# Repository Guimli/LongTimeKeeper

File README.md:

# LongTimeKeeper

**LongTimeKeeper** is a drop-in replacement for the STMicroelectronics **M48T58 / M48T58Y TIMEKEEPER® NVRAM** (8 K × 8 battery-backed SRAM with real-time clock) in its 28-pin 600 mil PCDIP "CAPHAT" package.

The original PCDIP part has its lithium cell sealed in the package. When the cell runs flat, the chip loses both the clock and the SRAM contents, and the whole IC has to be replaced. LongTimeKeeper uses the surface-mount **M48T58Y in SOH28** instead. That package normally takes an ST SNAPHAT® battery/crystal top. Here the SNAPHAT is replaced by:

- a discrete **32.768 kHz crystal**, and
- a **user-replaceable 1/2 AA 3.6 V lithium cell** in a Keystone holder. The cell is a Tadiran **SL-850/S** from the SL-800 XOL (eXtended Operating Life) series, rated 1.2 Ah. This series has a very low self-discharge rate.

The cell has a much larger capacity than the original internal cell, and you can swap it without desoldering anything or losing the board's socketed footprint.

## How it works

The adapter is a stack of two PCBs:

| Board | KiCad project | Role |
|---|---|---|
| **Bottom** | `LongTimeKeeper_Bottom/LongTimekeeper_Bottom.kicad_pro` | DIP-28 (15.24 mm) pin-out that plugs into the original M48T58 socket. It carries the M48T58Y-SOH28 (U7), the 32.768 kHz crystal (Y1) on the SNAPHAT X1/X2 contacts, and a 4-pad battery connector (BT1) wired to the SNAPHAT BAT+/BAT- contacts. |
| **Up** (battery) | `LongTimeKeeper_Up/TimekeeperBat_Up.kicad_pro` | Carries the Keystone 108 1/2 AA holder with its 108C cover (BT1). It connects to the bottom board through 4 × 2.54 mm pins (J1, `Battery_PCB` footprint), which also hold the two boards together mechanically. |

Signal mapping: every DIP-28 pin of the original package (A0–A12, DQ0–DQ7, Ē1, E2, Ḡ, W̄, FT, VCC, VSS) is routed 1:1 to the matching pin of the SOH28 device, so the host system sees an unmodified M48T58. Both boards are 2-layer, 1.6 mm FR-4, and fit within the original DIP-28 footprint (about 18.4 × 36.3 mm).

The projects were created with **KiCad 10**.

## Bill of materials

Prices are **indicative, VAT included (TTC, 20 % French VAT), for 1 unit**, checked in October 2026 at DigiKey France, except where noted. Distributor prices change often, so check them before ordering.

| Qty | Ref. | Description | Manufacturer | Manufacturer P/N | Unit price TTC | Total TTC |
|---:|---|---|---|---|---:|---:|
| 1 | U7 | TIMEKEEPER® NVRAM 64 Kbit (8K×8) + RTC, 5 V, SOH28 (SNAPHAT socket) | STMicroelectronics | **M48T58Y-70MH1F** | 24.97 € | 24.97 € |
| 1 | Y1 | Crystal 32.768 kHz, ±20 ppm, 12.5 pF, SMD 3.2 × 1.5 mm (3215) | Epson | **FC-135 32.7680KA-A3** (Q13FC1350000400) | 2.81 € | 2.81 € |
| 1 | BT1 (Up) | Battery holder, 1 × 1/2 AA, through-hole | Keystone Electronics | **108** | 1.52 € | 1.52 € |
| 1 | BT1 (Up) | Battery holder cover, 1/2 AA | Keystone Electronics | **108C** | ≈ 0.58 € ¹ | 0.58 € |
| 1 | — | Lithium cell Li-SOCl₂ 3.6 V 1.2 Ah, 1/2 AA (ER14250), standard terminals (no tabs), **SL-800 XOL – extended operating life** (very low self-discharge) | Tadiran | **SL-850/S** | 14.56 € ⁴ | 14.56 € |
| 2 | U2 | Male pin header 1 × 14, 2.54 mm, vertical (DIP-28 legs) | Würth Elektronik | **61301411121** (WR-PHD) | ≈ 1.10 € ² | 2.20 € |
| 4 | J1 / BT1 | Single 2.54 mm pins for the board-to-board link (cut from a 1 × 40 strip) | Würth Elektronik | **61304011121** (WR-PHD 1 × 40) | ≈ 2.20 € ² (strip) | 2.20 € |
| | | | | | **Subtotal components** | **≈ 48.86 €** |
| 1 | — | PCB "Bottom", 2 layers, 1.6 mm, 18.4 × 36.3 mm (`Gerber/LongTimekeeper_Bottom_Gerber.zip`) | JLCPCB | — | ≈ 1.30 € ³ | 1.30 € |
| 1 | — | PCB "Up", 2 layers, 1.6 mm, 18.4 × 36.3 mm (`Gerber/TimekeeperBat_Up_Gerber.zip`) | JLCPCB | — | ≈ 1.30 € ³ | 1.30 € |
| | | | | | **Total per module** | **≈ 51.46 €** |

¹ TME price (0.48 € excl. VAT, sold in packs of 10).
² Estimated.
³ Per board, from a batch of 5 at JLCPCB, with shipping and VAT included. See [PCB cost estimate](#pcb-cost-estimate).
⁴ 1001Piles price (France, VAT included). Order the `/S` variant (standard terminals, no solder tabs) to fit the Keystone 108 holder. The `/T` variant has solder tabs and does not fit.

### PCB cost estimate

Both boards are small (about 18.4 × 36.3 mm, 6.7 cm² each), 2-layer, 1.6 mm FR-4, and use standard rules. They qualify for the cheapest prototype offers. Prices are indicative and VAT included (20 %). The two designs are ordered as two separate jobs.

| Fab | Order | Fabrication | Shipping + VAT (est.) | Total TTC | Per module (Bottom + Up) |
|---|---|---|---:|---:|---:|
| **JLCPCB** (China) | 5 × Bottom + 5 × Up, HASL, green | 2 × ~2 USD ≈ 3.70 € | ≈ 9 € (economy shipping) | **≈ 13 €** | **≈ 2.60 €** |
| **AISLER** (Germany) | 3 × Bottom + 3 × Up, 2-layer "Budget" | 2 × (12 € job fee + 3 × 6.7 cm² × 0.067 €/cm²) ≈ 26.70 € excl. VAT | included | **≈ 32 €** | **≈ 10.70 €** |

JLCPCB is the cheapest option, but the low price is mostly lost if you order only one module, because shipping is a fixed cost. AISLER is about four times more expensive per module, but it ships faster within the EU and charges no import fees. Use a quote calculator for an exact price: some options increase it, such as ENIG finish (flatter pads, which make the SOH28 easier to solder), a non-green soldermask or express shipping.

### Notes on component choice

- **Crystal:** the schematic only specifies "32.768 kHz" on a 3215 footprint. The M48T58 datasheet does not give a load capacitance for the SNAPHAT crystal. Check the clock accuracy after assembly, and if needed try a lower-load (6–7 pF) 3215 crystal.
- **Battery:** use the Tadiran **SL-850/S** long-life cell (SL-800 series), not a standard-series cell such as the TL-5902. Its very low self-discharge rate suits a back-up that only draws a few µA for many years. The footprint and 3D model use the 1/2 AA (ER14250) size. Use a 3.6 V **primary** lithium cell. Do **not** use a rechargeable 3.7 V Li-ion 14250 cell, because its voltage is too high for the VBAT input.
- **DIP legs:** standard square header pins match the 3D model. Turned (machined) pins are gentler on the original socket.

## Battery life estimate

The cell supplies the M48T58Y only while the host is switched off (VCC below the switchover voltage V<sub>SO</sub>). When the host is on, the chip runs from VCC and draws no current from the cell.

**Inputs**

| Parameter | Value | Source |
|---|---|---|
| SL-850 nominal capacity | 1.2 Ah (1 200 mAh) | Tadiran SL-850 datasheet |
| SL-800 (XOL) self-discharge at room temperature | ≈ 0.7 % per year (typical) → ≈ 8.4 mAh/year; ≤ 1 % per year (max.) → ≤ 12 mAh/year | Tadiran XOL series page / Tadiran catalogue |
| XOL rated operating life | up to **40 years** | Tadiran XOL series page |
| M48T58 battery current I<sub>BAT</sub> = I<sub>ARRAY</sub> + I<sub>CLOCK</sub> (64 Kbit, 4T cell), typical | 40 + 497 = **537 nA at 20 °C**; 511 + 619 = **1 130 nA at 70 °C** | ST AN1012, Table 3 |

The calculation follows the AN1012 formula, with the cell's self-discharge added to the battery current:

life (years) = capacity ÷ (8 760 h × (1 − VCC duty cycle) × I<sub>BAT</sub> + yearly self-discharge)

With a VCC duty cycle of 0 % (host always off), the M48T58Y draws 537 nA × 8 760 h ≈ **4.7 mAh/year** at 20 °C and 1 130 nA × 8 760 h ≈ **9.9 mAh/year** at 70 °C.

**Estimate** (host always off, 100 % battery backup)

| Temperature | I<sub>BAT</sub> | Typical self-discharge (0.7 %/year) | Worst-case self-discharge (1 %/year) |
|---|---:|---:|---:|
| 20 °C | 537 nA | 4.7 + 8.4 = 13.1 mAh/year → ≈ 92 years | 4.7 + 12 = 16.7 mAh/year → ≈ 72 years |
| 70 °C ¹ | 1 130 nA | 9.9 + 8.4 = 18.3 mAh/year → ≈ 66 years | 9.9 + 12 = 21.9 mAh/year → ≈ 55 years |

¹ The self-discharge figures are specified at room temperature. At 70 °C the cell's real self-discharge is higher, so this row overestimates the life.

**Conclusion.** Even with the host always off, the calculated life is far beyond the cell's rated life. The practical limit is therefore the cell's rated life, not its capacity: Tadiran rates the XOL series for **up to 40 years** of operation. Expect **about 40 years** at room temperature. For comparison, AN1012 (Table 13) gives the original M48T58 with its internal 48 mAh cell about 9.4 years (typical) at 20 °C and 4.8 years at 70 °C when the host is always off.

Factors that shorten this life:
- **Temperature.** Both the M48T58Y current and the cell's self-discharge rise with temperature, for example inside a closed, warm cabinet.
- **Leakage.** Flux residue or humidity on the board can create leakage paths. Clean the boards after soldering.

**Monitoring.** At each power-up, the M48T58Y sets its **battery low flag** (BL, bit D6 of register 1FFDh) when the cell is below about 2.5 V. Li-SOCl₂ cells keep a flat voltage of about 3.6 V almost until they are empty, so treat this flag as the signal to replace the SL-850.

## Assembly hints

1. Solder Y1 and U7 (SOH28) on the bottom board. Do **not** wave-solder the SOH28 package (see the ST datasheet).
2. Fit the two 1 × 14 headers on the bottom board, with the long pins pointing down, to form the DIP-28 legs.
3. Solder the Keystone 108 holder on the Up board, then the 4 link pins. Stack the Up board on the bottom board and solder the pins.
4. Insert the SL-850/S cell with the polarity marked on the holder, then snap on the 108C cover.
5. Plug the module into the original M48T58 socket, with pin 1 at the notched end.

## Datasheets

- [M48T58 / M48T58Y – STMicroelectronics](Datasheet/M48T58.pdf)
- [AN1012 – Predicting the battery life and data retention period of NVRAMs and serial RTCs – STMicroelectronics](Datasheet/AN1012.pdf)
- [Keystone 108 battery holder](Datasheet/108-745412.pdf)
- [Keystone 108C cover](Datasheet/08C-745621.pdf)
- [Tadiran SL-850 (XOL – extended operating life)](Datasheet/tadiran_sl-850.pdf). This page is taken from the Tadiran Lithium Batteries Product Data Catalogue and also shows the SL-861.
- [Tadiran TL-5902](Datasheet/tadiran_tl5902-1214159.pdf). This is the standard-series datasheet, kept for reference.

## License

Copyright © 2026 Guimli.

This hardware design is licensed under the **CERN Open Hardware Licence Version 2 – Strongly Reciprocal** ([CERN-OHL-S-2.0](LICENSE)).

You may redistribute and modify this source and make products using it under the terms of the CERN-OHL-S v2. This source is distributed WITHOUT ANY EXPRESS OR IMPLIED WARRANTY, INCLUDING OF MERCHANTABILITY, SATISFACTORY QUALITY AND FITNESS FOR A PARTICULAR PURPOSE. See the CERN-OHL-S v2 for applicable conditions.

Third-party documents in `Datasheet/` and 3D models from manufacturers remain the property of their respective owners and are not covered by this licence.

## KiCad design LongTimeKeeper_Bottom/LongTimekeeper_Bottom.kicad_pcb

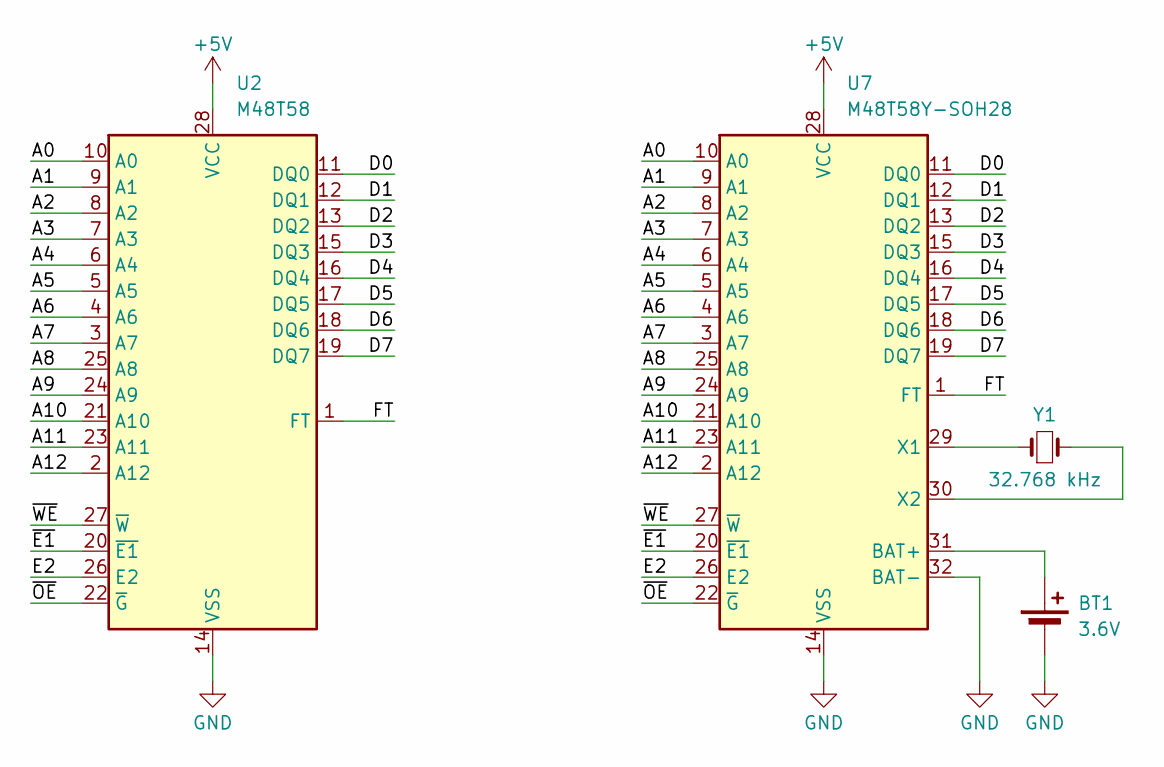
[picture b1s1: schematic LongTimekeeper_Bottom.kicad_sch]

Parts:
BT1: 3.6V; Battery_PCB
U2: M48T58; DIP-28_W15.24mm_Socket
U7: M48T58Y-SOH28; SOH-28_8.56x18.1mm_P1.27mm
Y1: 32.768 kHz; Crystal_SMD_3215-2Pin_3.2x1.5mm

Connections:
+5V: U2.28 (VCC), U7.28 (VCC)
/A0: U2.10 (A0), U7.10 (A0)
/A1: U2.9 (A1), U7.9 (A1)
/A2: U2.8 (A2), U7.8 (A2)
/A3: U2.7 (A3), U7.7 (A3)
/A4: U2.6 (A4), U7.6 (A4)
/A5: U2.5 (A5), U7.5 (A5)
/A6: U2.4 (A6), U7.4 (A6)
/A7: U2.3 (A7), U7.3 (A7)
/A8: U2.25 (A8), U7.25 (A8)
/A9: U2.24 (A9), U7.24 (A9)
/A10: U2.21 (A10), U7.21 (A10)
/A11: U2.23 (A11), U7.23 (A11)
/A12: U2.2 (A12), U7.2 (A12)
/D0: U2.11 (DQ0), U7.11 (DQ0)
/D1: U2.12 (DQ1), U7.12 (DQ1)
/D2: U2.13 (DQ2), U7.13 (DQ2)
/D3: U2.15 (DQ3), U7.15 (DQ3)
/D4: U2.16 (DQ4), U7.16 (DQ4)
/D5: U2.17 (DQ5), U7.17 (DQ5)
/D6: U2.18 (DQ6), U7.18 (DQ6)
/D7: U2.19 (DQ7), U7.19 (DQ7)
/E2: U2.26 (E2), U7.26 (E2)
/FT: U2.1 (FT), U7.1 (FT)
/~E1: U2.20 (~E1), U7.20 (~E1)
/~OE: U2.22 (~G), U7.22 (~G)
/~WE: U2.27 (~W), U7.27 (~W)
GND: BT1.2 (-), U2.14 (VSS), U7.14 (VSS), U7.32 (BAT-)
unnamed: BT1.1 (+), U7.31 (BAT+)
unnamed: U7.29 (X1), Y1.1
unnamed: U7.30 (X2), Y1.2

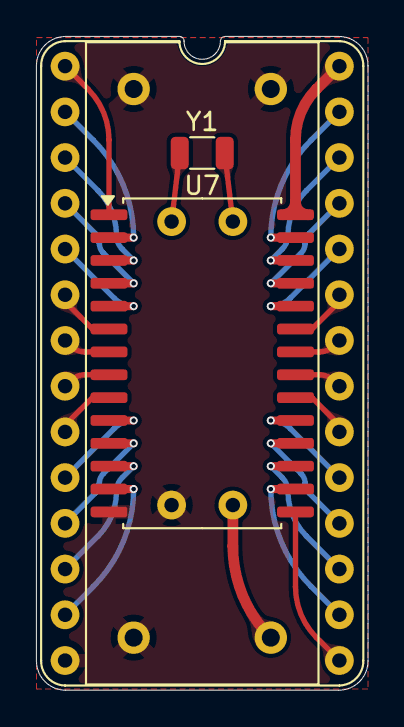
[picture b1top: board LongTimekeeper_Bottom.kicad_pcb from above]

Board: 2 copper layers, 18.4 x 36.3 mm, 5 parts (1 on the bottom side), 31 nets.

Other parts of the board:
kibuzzard-6AB09B05: G***; kibuzzard-6AB09B05
